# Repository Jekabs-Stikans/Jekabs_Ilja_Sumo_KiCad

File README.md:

# Sumo robota projekts kursā EIB2

# Darba autori Jēkabs Stikāns un Iļja Viļevka

Repozitorija satur visus ar šo projektu saistītos KiCad failus

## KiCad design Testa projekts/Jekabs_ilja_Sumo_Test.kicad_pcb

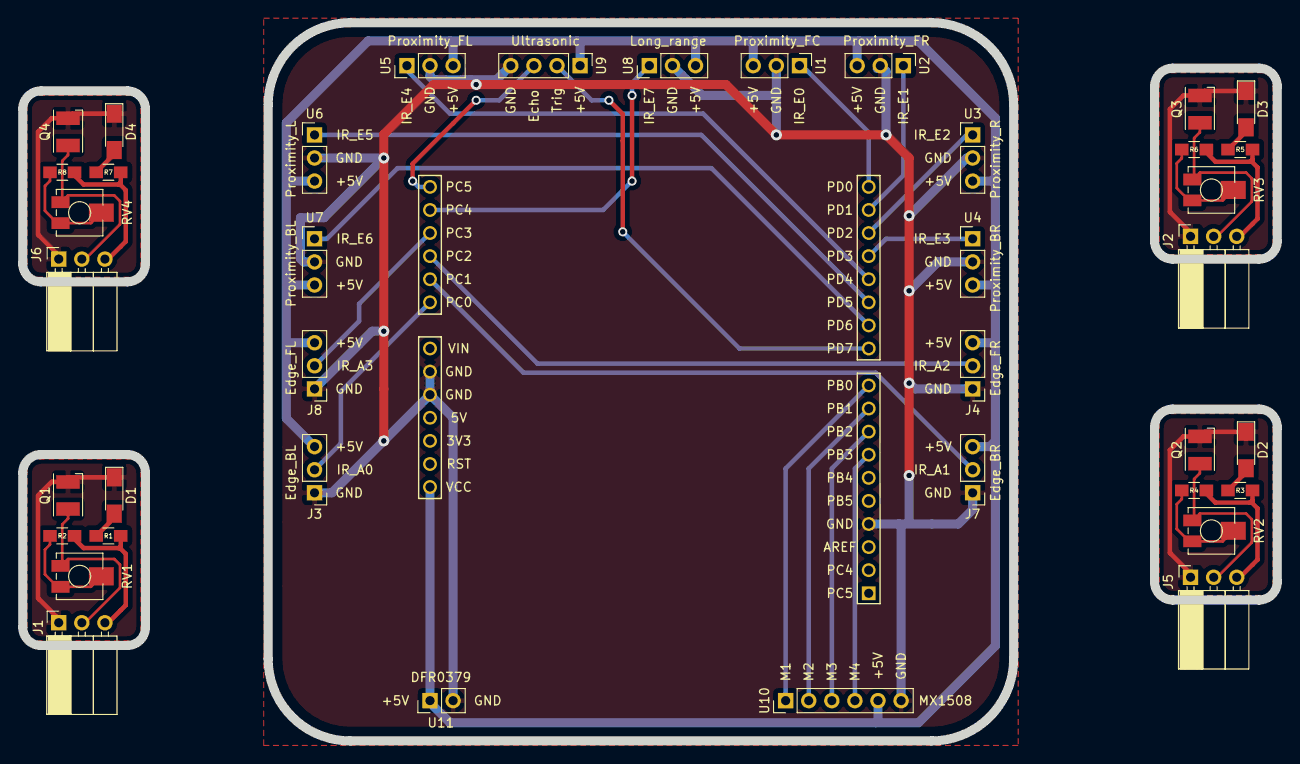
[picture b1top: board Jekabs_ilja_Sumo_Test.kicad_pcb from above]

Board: 2 copper layers, 138.0 x 79.0 mm, 40 parts (0 on the bottom side), 28 nets.

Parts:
D1, D2, D3, D4: LED_IR; LED_1206_HandSoldering
J1, J2, J5, J6: Conn_01x03; Socket_Strip_Angled_1x03_Pitch2.54mm
J3: Edge_BL; Socket_Strip_Straight_1x03_Pitch2.54mm
J4: Edge_FR; Socket_Strip_Straight_1x03_Pitch2.54mm
J7: Edge_BR; Socket_Strip_Straight_1x03_Pitch2.54mm
J8: Edge_FL; Socket_Strip_Straight_1x03_Pitch2.54mm
MCU1: ATmega328P_Shield; ATmega328P_Xplained_mini
Q1, Q2, Q3, Q4: Q_Photo; LED_PLCC-2
R1, R3, R5, R7: 100R; R_0805_HandSoldering
R2, R4, R6, R8: 10k; R_0805_HandSoldering
RV1, RV2, RV3, RV4: 10k; Potentiometer_Trimmer_Vishay_TS53YL
U1: Proximity_FC; Socket_Strip_Straight_1x03_Pitch2.54mm
U2: Proximity_FR; Socket_Strip_Straight_1x03_Pitch2.54mm
U3: Proximity_R; Socket_Strip_Straight_1x03_Pitch2.54mm
U4: Proximity_BR; Socket_Strip_Straight_1x03_Pitch2.54mm
U5: Proximity_FL; Socket_Strip_Straight_1x03_Pitch2.54mm
U6: Proximity_L; Socket_Strip_Straight_1x03_Pitch2.54mm
U7: Proximity_BL; Socket_Strip_Straight_1x03_Pitch2.54mm
U8: Long_range; Socket_Strip_Straight_1x03_Pitch2.54mm
U9: Ultrasonic; Socket_Strip_Straight_1x04_Pitch2.54mm
U10: MX1508; Socket_Strip_Straight_1x06_Pitch2.54mm
U11: DFR0379; Socket_Strip_Straight_1x02_Pitch2.54mm

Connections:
+5V: J1.3, J2.3, J3.3, J4.3, J5.3, J6.3, J7.3, J8.3, MCU1.20, R1.1, R2.1, R3.1, R4.1, R5.1, R6.1, R7.1, R8.1, U1.3, U2.3, U3.3, U4.3, U5.3, U6.3, U7.3, U8.3, U9.1, U10.9, U11.3
/Echo: MCU1.32, U9.3
/Trig: MCU1.11, U9.2
GND: D1.1, D2.1, D3.1, D4.1, J1.1, J2.1, J3.1, J4.1, J5.1, J6.1, J7.1, J8.1, MCU1.4, MCU1.24, MCU1.25, Q1.1, Q2.1, Q3.1, Q4.1, U1.2, U2.2, U3.2, U4.2, U5.2, U6.2, U7.2, U8.2, U9.4, U10.10, U11.4
IR_A0: J1.2, J3.2, MCU1.27, Q1.2, RV1.3
IR_A1: J5.2, J7.2, MCU1.28, Q2.2, RV2.3
IR_A2: J2.2, J4.2, MCU1.29, Q3.2, RV3.3
IR_A3: J6.2, J8.2, MCU1.30, Q4.2, RV4.3
IR_E0: MCU1.18, U1.1
IR_E1: MCU1.17, U2.1
IR_E2: MCU1.16, U3.1
IR_E3: MCU1.15, U4.1
IR_E4: MCU1.14, U5.1
IR_E5: MCU1.13, U6.1
IR_E6: MCU1.12, U7.1
IR_E7: MCU1.31, U8.1
M1: MCU1.10, U10.1
M2: MCU1.9, U10.2
M3: MCU1.8, U10.3
M4: MCU1.7, U10.4
unnamed: D1.2, R1.2
unnamed: D2.2, R3.2
unnamed: D3.2, R5.2
unnamed: D4.2, R7.2
unnamed: R2.2, RV1.1, RV1.2
unnamed: R4.2, RV2.1, RV2.2
unnamed: R6.2, RV3.1, RV3.2
unnamed: R8.2, RV4.1, RV4.2

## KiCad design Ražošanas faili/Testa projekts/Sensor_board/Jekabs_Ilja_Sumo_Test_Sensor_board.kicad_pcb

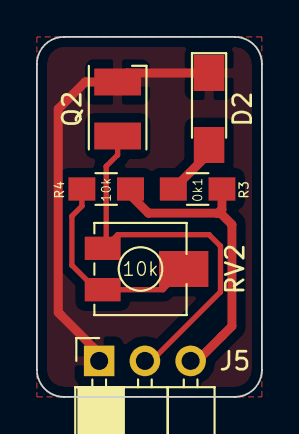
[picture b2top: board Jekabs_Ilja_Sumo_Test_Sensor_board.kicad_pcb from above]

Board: 2 copper layers, 12.5 x 20.0 mm, 6 parts (0 on the bottom side), 5 nets.

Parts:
D2: LED_IR; LED_1206_HandSoldering
J5: Conn_01x03; Socket_Strip_Angled_1x03_Pitch2.54mm
Q2: Q_Photo; LED_PLCC-2
R3: 0k1; R_0805_HandSoldering
R4: 10k; R_0805_HandSoldering
RV2: 10k; Potentiometer_Trimmer_Vishay_TS53YL

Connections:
+5V: J5.3, R3.1, R4.1
GND: D2.1, J5.1, Q2.1
IR_A1: J5.2, Q2.2, RV2.3
unnamed: D2.2, R3.2
unnamed: R4.2, RV2.1, RV2.2

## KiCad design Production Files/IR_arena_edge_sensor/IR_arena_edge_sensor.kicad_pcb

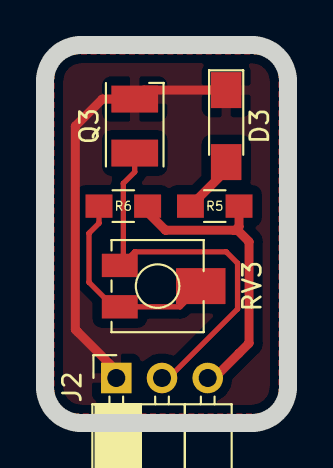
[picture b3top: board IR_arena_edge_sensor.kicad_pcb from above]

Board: 2 copper layers, 13.5 x 21.0 mm, 6 parts (0 on the bottom side), 5 nets.

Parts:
D3: LED_IR; LED_1206_HandSoldering
J2: Conn_01x03; Socket_Strip_Angled_1x03_Pitch2.54mm
Q3: Q_Photo; LED_PLCC-2
R5: 100R; R_0805_HandSoldering
R6: 10k; R_0805_HandSoldering
RV3: 10k; Potentiometer_Trimmer_Vishay_TS53YL

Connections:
+5V: J2.3, R5.1, R6.1
GND: D3.1, J2.1, Q3.1
IR_A2: J2.2, Q3.2, RV3.3
unnamed: D3.2, R5.2
unnamed: R6.2, RV3.1, RV3.2

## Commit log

2021-03-18 Test PCB Production files generated
2021-03-18 Folder reorganisation
2021-03-18 Updated README.md location
2021-03-19 Projekta nosaukuma maiņa un ražošanas PCB failu korekcijas
2021-03-19 Maza nosaukumu korekcija
2021-03-24 Testa principiālās shēmas pdf sagatave
2021-03-24 Nelielas failu organizācijas izmaiņas
